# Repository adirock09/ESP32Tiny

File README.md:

# ESP32
<br>

<br>
This project is a custom-designed breakout board for the ESP32-S3 chip, created using KiCad . The board features native USB-C programming support, and includes an integrated Li-Ion battery

## Hardware

- **Features**

-ESP32-S3 Microcontroller

-USB-C Port

  Used for both power input and firmware flashing

-Li-Ion Battery Charging Circuit

  Integrated charger IC with status indicators

  Supports single-cell Li-Ion/LiPo batteries

-Compact Breakout Form Factor

  All key GPIOs broken out

## Bill of Materials (BOM)

| Serial Num | Description | Total (USD) | 
|----:|--------------------------|-------------|
| 1  | PCB and Assembly  |33.56 |
| 2 | Shipping JLCPCB  |14.27 |

### 💰 Cost Summary

- **Estimated Total Cost ( PCB ASSEMBLY + Shipping):** **$47.83	 USD**

## Schematic and PCB
<br>

<br>

<br>

## 3D Model
<br>

<br>

<br>

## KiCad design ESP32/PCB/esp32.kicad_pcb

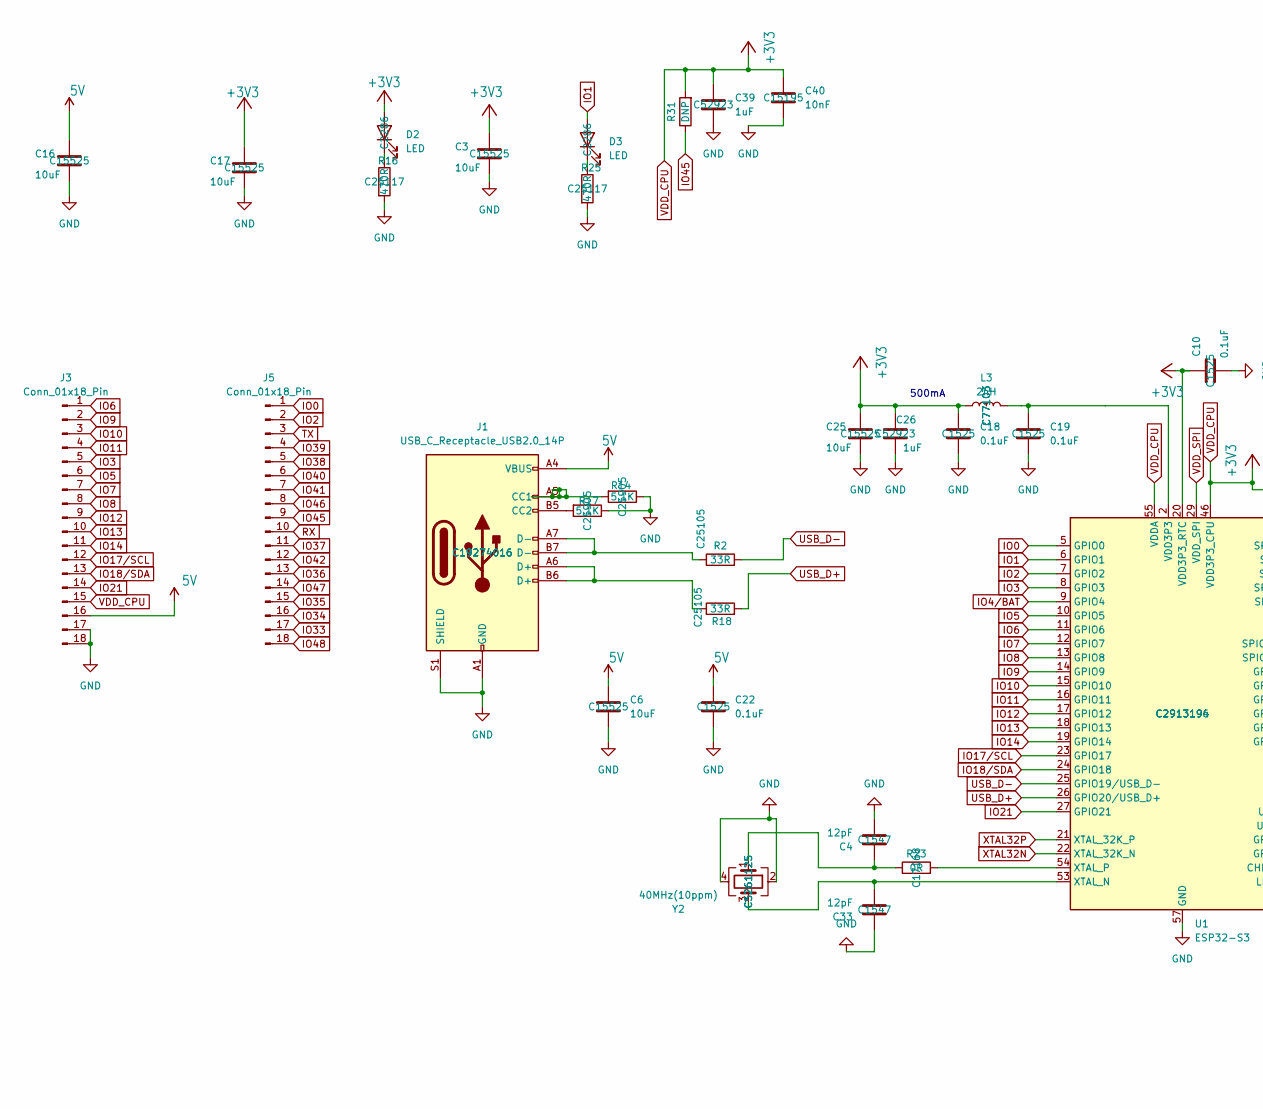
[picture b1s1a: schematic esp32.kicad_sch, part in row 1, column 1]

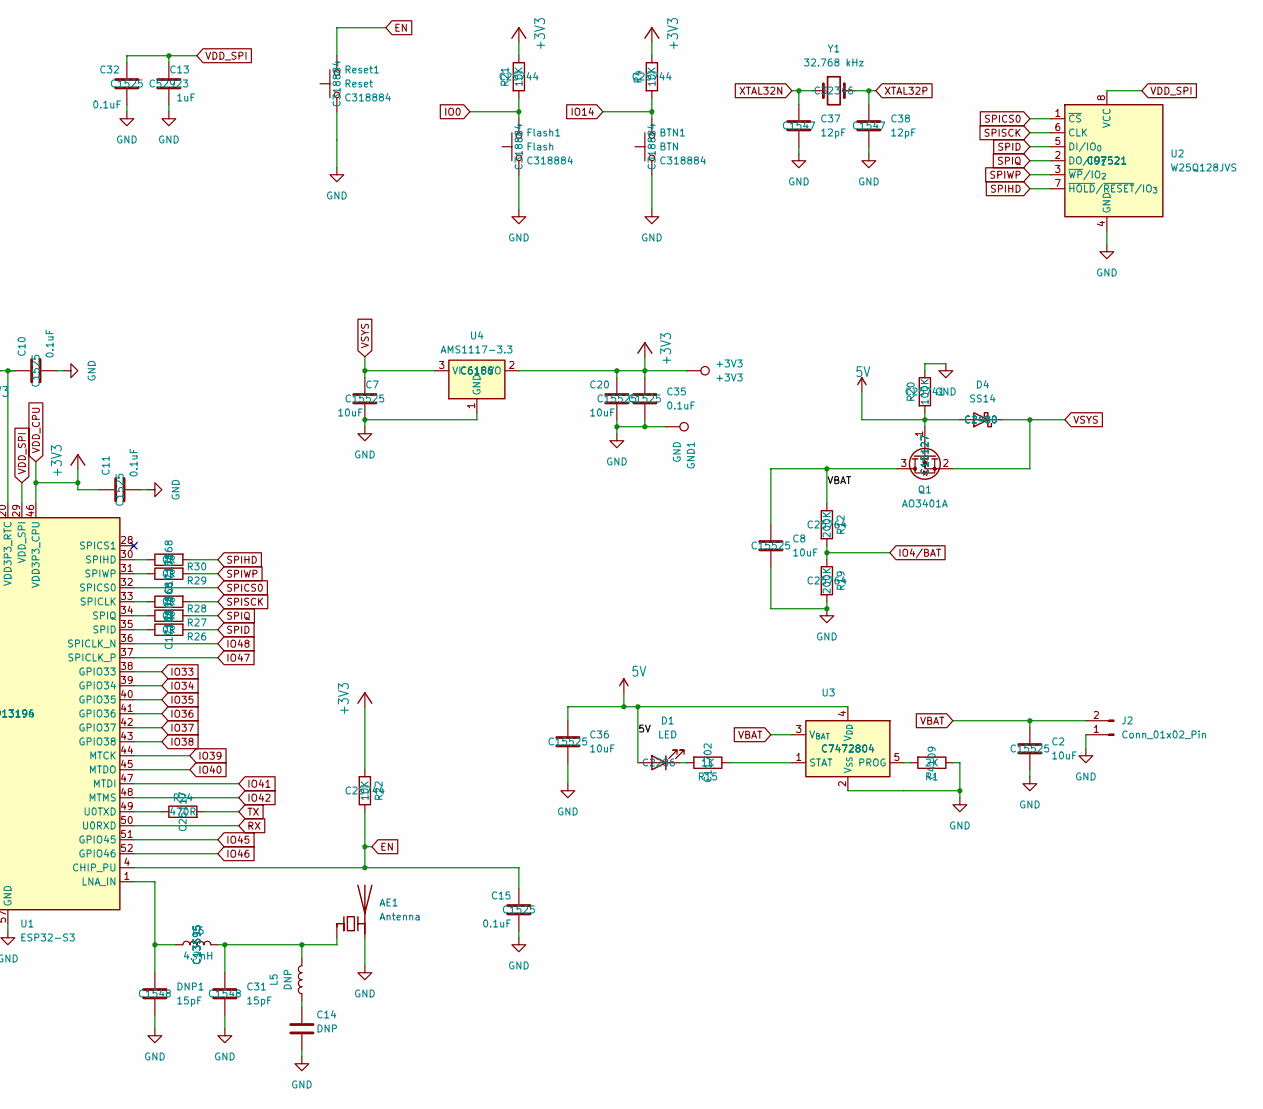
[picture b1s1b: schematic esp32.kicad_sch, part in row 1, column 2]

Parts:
+3V3: +3V3; TestPoint_Pad_D1.0mm
AE1: Antenna; Texas_SWRA117D_2.4GHz_Left
BTN1: BTN; SW_Push_1P1T_XKB_TS-1187A; MNF PART NUMBER C318884; LCSC C318884
C2, C3, C6, C7, C8, C16, C17, C20, C25, C36: 10uF; C_0402_1005Metric; MNF PART NUMBER C15525; LCSC C15525
C4, C33, C37, C38: 12pF; C_0402_1005Metric; MNF PART NUMBER C1547; LCSC C1547
C10, C11, C15, C18, C19, C22, C32, C35: 0.1uF; C_0402_1005Metric; MNF PART NUMBER C1525; LCSC C1525
C13, C26, C39: 1uF; C_0402_1005Metric; MNF PART NUMBER C52923; LCSC C52923
C14: DNP; C_0402_1005Metric
C31: 15pF; C_0402_1005Metric; MNF PART NUMBER C1548; LCSC C1548
C40: 10nF; C_0402_1005Metric; MNF PART NUMBER C15195; LCSC C15195
D1, D2, D3: LED; LED_0603_1608Metric; MNF PART NUMBER C2286; LCSC C2286
D4: SS14; D_SMA; MNF PART NUMBER C2480; LCSC C2480
DNP1: 15pF; C_0402_1005Metric; MNF PART NUMBER C1548; LCSC C1548
Flash1: Flash; SW_Push_1P1T_XKB_TS-1187A; MNF PART NUMBER C318884; LCSC C318884
GND1: GND; TestPoint_Pad_D1.0mm
J1: USB_C_Receptacle_USB2.0_14P; USB_C_Receptacle_HCTL_HC-TYPE-C-16P-01A; MNF PART NUMBER C19274016; LCSC C19274016
J2: Conn_01x02_Pin; PinSocket_1x02_P2.54mm_Vertical
J3, J5: Conn_01x18_Pin; PinHeader_1x18_P2.54mm_Vertical
L3: 2nH; L_0402_1005Metric; MNF PART NUMBER C77103; LCSC C77103
L5: DNP; L_0402_1005Metric
L6: 4.7nH; L_0402_1005Metric; MNF PART NUMBER C13595; LCSC C13595
Q1: AO3401A; SOT-23; MNF PART NUMBER C15127; LCSC C15127
R1: 2K; R_0402_1005Metric; MNF PART NUMBER C4109; LCSC C4109
R2, R18: 33R; R_0402_1005Metric; MNF PART NUMBER C25105; LCSC C25105
R4, R21, R22: 10K; R_0402_1005Metric; MNF PART NUMBER C25744; LCSC C25744
R12, R19: 200K; R_0402_1005Metric; MNF PART NUMBER C25764; LCSC C25764
R14, R17: 5.1K; R_0402_1005Metric; MNF PART NUMBER C25905; LCSC C25905
R15: 1K; R_0402_1005Metric; MNF PART NUMBER C11702; LCSC C11702
R16, R24, R25: 470R; R_0402_1005Metric; MNF PART NUMBER C25117; LCSC C25117
R20: 100K; R_0402_1005Metric; MNF PART NUMBER C25741; LCSC C25741
R23, R26, R27, R28, R29, R30: 0R; R_0402_1005Metric; MNF PART NUMBER C17168; LCSC C17168
R31: DNP; R_0402_1005Metric
Reset1: Reset; SW_Push_1P1T_XKB_TS-1187A; MNF PART NUMBER C318884; LCSC C318884
U1: ESP32-S3; QFN-56-1EP_7x7mm_P0.4mm_EP4x4mm; MNF PART NUMBER C2913196; LCSC C2913194
U2: W25Q128JVS; SOIC-8_5.3x5.3mm_P1.27mm; MNF PART NUMBER C97521; LCSC C97521
U3: MCP73831-2-OT; SOT-23-5; MNF PART NUMBER C7472804; LCSC C7472804
U4: AMS1117-3.3; SOT-223-3_TabPin2; MNF PART NUMBER C6186; LCSC C6186
Y1: 32.768 kHz; Crystal_SMD_3215-2Pin_3.2x1.5mm; MNF PART NUMBER C32346; LCSC C32346
Y2: 40MHz(10ppm); Crystal_SMD_2520-4Pin_2.5x2.0mm; MNF PART NUMBER C5261125; LCSC C5261125

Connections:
5V: C6.1, C16.1, C22.1, C36.1, D1.2 (A), D4.2 (A), J1.A4 (VBUS), J1.A9 (VBUS), J1.B4 (VBUS), J1.B9 (VBUS), J3.16, Q1.1 (G), R20.2, U3.4 (V_{DD})
EN: C15.1, R22.1, Reset1.2, U1.4 (CHIP_PU)
GND: AE1.2 (PCB_Trace), BTN1.1, C2.2, C3.2, C4.2, C6.2, C7.2, C8.2, C10.2, C11.2, C13.2, C14.2, C15.2, C16.2, C17.2, C18.2, C19.2, C20.2, C22.2, C25.2, C26.2, C31.2, C32.2, C33.1, C35.2, C36.2, C37.2, C38.2, C39.2, C40.2, DNP1.2, Flash1.1, GND1.1, J1.A1 (GND), J1.A12 (GND), J1.B1 (GND), J1.B12 (GND), J1.S1 (SHIELD), J2.1, J3.17, J3.18, R1.1, R14.1, R16.2, R17.1, R19.2, R20.1, R25.2, Reset1.1, U1.57 (GND), U2.4 (GND), U3.2 (V_{SS}), U4.1 (GND), Y2.2, Y2.4
IO0: Flash1.2, J5.1, R21.2, U1.5 (GPIO0)
IO1: D3.2 (A), U1.6 (GPIO1)
IO2: J5.2, U1.7 (GPIO2)
IO3: J3.5, U1.8 (GPIO3)
IO4/BAT: R12.2, R19.1, U1.9 (GPIO4)
IO5: J3.6, U1.10 (GPIO5)
IO6: J3.1, U1.11 (GPIO6)
IO7: J3.7, U1.12 (GPIO7)
IO8: J3.8, U1.13 (GPIO8)
IO9: J3.2, U1.14 (GPIO9)
IO10: J3.3, U1.15 (GPIO10)
IO11: J3.4, U1.16 (GPIO11)
IO12: J3.9, U1.17 (GPIO12)
IO13: J3.10, U1.18 (GPIO13)
IO14: BTN1.2, J3.11, R4.2, U1.19 (GPIO14)
IO17/SCL: J3.12, U1.23 (GPIO17)
IO18/SDA: J3.13, U1.24 (GPIO18)
IO21: J3.14, U1.27 (GPIO21)
IO33: J5.17, U1.38 (GPIO33)
IO34: J5.16, U1.39 (GPIO34)
IO35: J5.15, U1.40 (GPIO35)
IO36: J5.13, U1.41 (GPIO36)
IO37: J5.11, U1.42 (GPIO37)
IO38: J5.5, U1.43 (GPIO38)
IO39: J5.4, U1.44 (MTCK)
IO40: J5.6, U1.45 (MTDO)
IO41: J5.7, U1.47 (MTDI)
IO42: J5.12, U1.48 (MTMS)
IO45: J5.9, R31.1, U1.51 (GPIO45)
IO46: J5.8, U1.52 (GPIO46)
IO47: J5.14, U1.37 (SPICLK_P)
IO48: J5.18, U1.36 (SPICLK_N)
unnamed: AE1.1 (FEED), C31.1, L5.2, L6.2
unnamed: C4.1, R23.1, Y2.1
unnamed: C14.1, L5.1
unnamed: C19.1, L3.2, U1.2 (VDD3P3), U1.3 (VDD3P3)
unnamed: D1.1 (K), R15.2
unnamed: D2.1 (K), R16.1
unnamed: D3.1 (K), R25.1
unnamed: J1.A5 (CC1), R14.2
unnamed: J1.B5 (CC2), R17.2
unnamed: J1.A6 (D+), J1.B6 (D+), R18.1
unnamed: J1.A7 (D-), J1.B7 (D-), R2.1
unnamed: DNP1.1, L6.1, U1.1 (LNA_IN)
unnamed: R28.1, U1.33 (SPICLK)
unnamed: R26.1, U1.35 (SPID)
unnamed: R30.1, U1.30 (SPIHD)
unnamed: R27.1, U1.34 (SPIQ)
unnamed: R29.1, U1.31 (SPIWP)
unnamed: R24.1, U1.49 (U0TXD)
unnamed: C33.2, U1.53 (XTAL_N), Y2.3
unnamed: R23.2, U1.54 (XTAL_P)
unnamed: R1.2, U3.5 (PROG)
unnamed: R15.1, U3.1 (STAT)
RX: J5.10, U1.50 (U0RXD)
SPICS0: U1.32 (SPICS0), U2.1 (~CS)
SPID: R26.2, U2.5 (DI/IO_{0})
SPIHD: R30.2, U2.7 (~HOLD/~RESET/IO_{3})
SPIQ: R27.2, U2.2 (DO/IO_{1})
SPISCK: R28.2, U2.6 (CLK)
SPIWP: R29.2, U2.3 (~WP/IO_{2})
TX: J5.3, R24.2
USB_D+: R18.2, U1.26 (GPIO20/USB_D+)
USB_D-: R2.2, U1.25 (GPIO19/USB_D-)
VBAT: C2.1, C8.1, J2.2, Q1.3 (D), R12.1, U3.3 (V_{BAT})
VDD_CPU: +3V3.1, C3.1, C10.1, C11.1, C17.1, C18.1, C20.1, C25.1, C26.1, C35.1, C39.1, C40.1, D2.2 (A), J3.15, L3.1, R4.1, R21.1, R22.2, R31.2, U1.20 (VDD3P3_RTC), U1.46 (VDD3P3_CPU), U1.55 (VDDA), U1.56 (VDDA), U4.2 (VO)
VDD_SPI: C13.1, C32.1, U1.29 (VDD_SPI), U2.8 (VCC)
VSYS: C7.1, D4.1 (K), Q1.2 (S), U4.3 (VI)
XTAL32N: C37.1, U1.22 (XTAL_32K_N), Y1.1
XTAL32P: C38.1, U1.21 (XTAL_32K_P), Y1.2

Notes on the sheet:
500mA

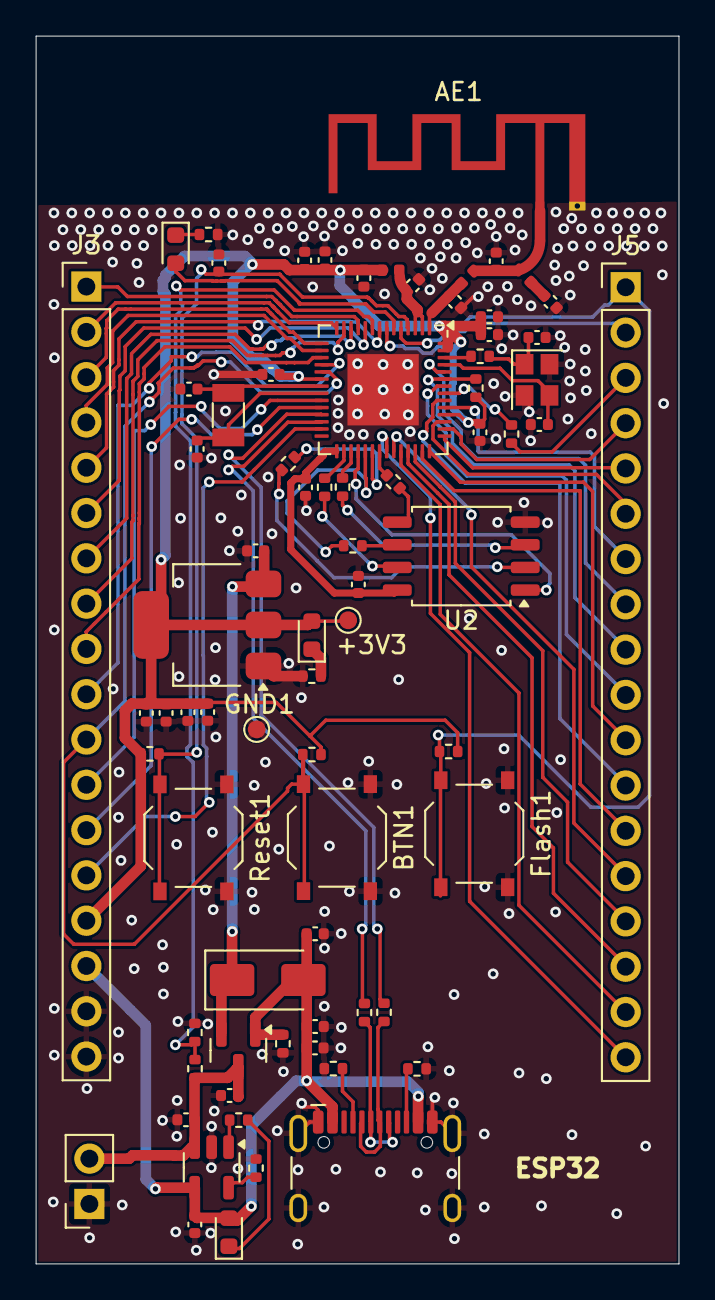
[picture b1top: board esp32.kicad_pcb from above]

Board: 2 copper layers, 36.0 x 68.8 mm, 75 parts (0 on the bottom side), 73 nets.

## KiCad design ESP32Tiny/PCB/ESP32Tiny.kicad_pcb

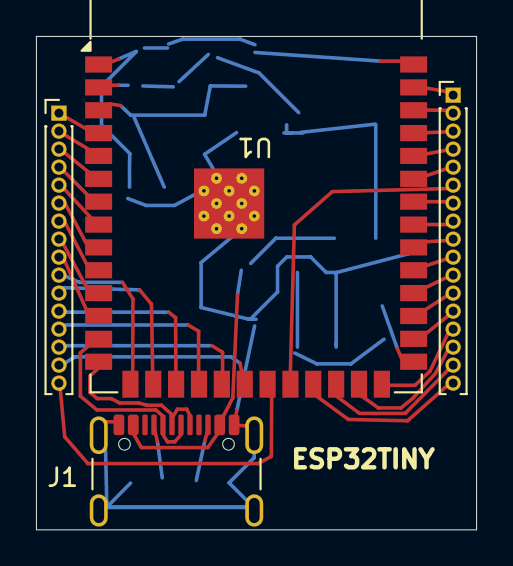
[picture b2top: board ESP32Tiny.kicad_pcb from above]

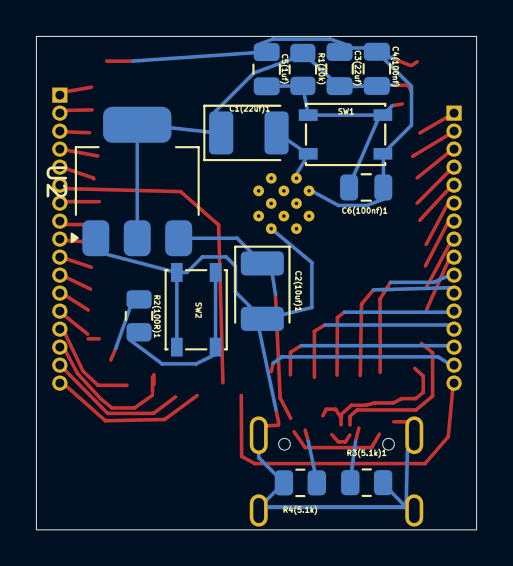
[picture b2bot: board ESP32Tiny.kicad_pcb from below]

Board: 2 copper layers, 24.5 x 27.4 mm, 17 parts (13 on the bottom side), 43 nets.

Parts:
C1(22uf)1, C2(10uf)1: C_Polarized; CP_EIA-3528-21_Kemet-B
C3(22uf), C4(100nf), C5(1uf), C6(100nf)1: C; C_0805_2012Metric
IO1: Conn_01x16_Pin; PinHeader_1x16_P1.00mm_Vertical
J1: USB_C_Receptacle_USB2.0_16P; USB_C_Receptacle_GCT_USB4105-xx-A_16P_TopMnt_Horizontal
J3: Conn_01x17_Pin; PinHeader_1x17_P1.00mm_Vertical
R1(10k), R2(100R)1, R3(5.1k)1, R4(5.1k): R; R_0805_2012Metric
SW1, SW2: SW_Push; SW_SPST_PTS810
U1: ESP32-S3-WROOM-1
U2: AMS1117-3.3; SOT-223-3_TabPin2

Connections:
+3.3V: C1(22uf)1.1, C3(22uf).1, C4(100nf).1, R1(10k).1, U1.2 (3V3), U2.2 (VO)
+5V: C2(10uf)1.1, J1.A4 (VBUS), J1.A9 (VBUS), J1.B4 (VBUS), J1.B9 (VBUS), U2.3 (VI)
BOOT: R2(100R)1.1, U1.27 (IO0)
D+: J1.A6 (D+), J1.B6 (D+), U1.14 (USB_D+)
D-: J1.A7 (D-), J1.B7 (D-), U1.13 (USB_D-)
EN: C5(1uf).1, C6(100nf)1.1, R1(10k).2, SW1.1, U1.3 (EN)
GND: C1(22uf)1.2, C2(10uf)1.2, C3(22uf).2, C4(100nf).2, C5(1uf).2, C6(100nf)1.2, J1.A1 (GND), J1.A12 (GND), J1.B1 (GND), J1.B12 (GND), J1.S1 (SHIELD), R3(5.1k)1.2, R4(5.1k).2, SW1.2, SW2.2, U1.1 (GND), U1.40 (GND), U1.41 (GND), U2.1 (GND)
unnamed: IO1.1, U1.4 (IO4)
unnamed: IO1.2, U1.5 (IO5)
unnamed: IO1.3, U1.6 (IO6)
unnamed: IO1.4, U1.7 (IO7)
unnamed: IO1.5, U1.8 (IO15)
unnamed: IO1.6, U1.9 (IO16)
unnamed: IO1.7, U1.10 (IO17)
unnamed: IO1.8, U1.11 (IO18)
unnamed: IO1.9, U1.12 (IO8)
unnamed: IO1.10, U1.15 (IO3)
unnamed: IO1.11, U1.16 (IO46)
unnamed: IO1.12, U1.17 (IO9)
unnamed: IO1.13, U1.18 (IO10)
unnamed: IO1.14, U1.19 (IO11)
unnamed: IO1.15, U1.20 (IO12)
unnamed: IO1.16, U1.21 (IO13)
unnamed: J1.A5 (CC1), R3(5.1k)1.1
unnamed: J1.B5 (CC2), R4(5.1k).1
unnamed: J3.1, U1.39 (IO1)
unnamed: J3.2, U1.38 (IO2)
unnamed: J3.3, U1.37 (TXD0)
unnamed: J3.4, U1.36 (RXD0)
unnamed: J3.5, U1.35 (IO42)
unnamed: J3.6, U1.22 (IO14)
unnamed: J3.7, U1.34 (IO41)
unnamed: J3.8, U1.33 (IO40)
unnamed: J3.9, U1.32 (IO39)
unnamed: J3.10, U1.31 (IO38)
unnamed: J3.11, U1.30 (IO37)
unnamed: J3.12, U1.29 (IO36)
unnamed: J3.13, U1.28 (IO35)
unnamed: J3.14, U1.26 (IO45)
unnamed: J3.15, U1.25 (IO48)
unnamed: J3.16, U1.24 (IO47)
unnamed: J3.17, U1.23 (IO21)
unnamed: R2(100R)1.2, SW2.1
